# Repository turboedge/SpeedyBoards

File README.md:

# SpeedyBoards
WTMtronics has developed several EMS PCBs designed to use the Speeduino firmware.
The Speeduino code is available here [Speeduino](https://github.com/noisymime/speeduino), but the easiest way to load the code onto your ECU is to use [SpeedyLoader](https://github.com/speeduino/SpeedyLoader).
## Ocelot
The latest ECU designed by WTMtronics builds on the UA4C that came before it, and in fact if you compare the two side by side you will see many similarities. However there have been many improvements over the previous model which are outlined in the list below.
- Automotive connector
- Reduced size
- Integrated microcontroller
- VSS input
- Flyback diodes
- Reset button

The reset button was added as the only reset connection made to the microcontroller to prevent unwanted resets from USB connected devices. There is a caveat to this arrangement though. While the first time a firmware is loaded it will go on without intervention, subsequent times will require the user to hold the reset button down then release the button when the program starts the upload process. If the upload does not start right away go back and try again.

The Ocelot uses the Silicon Labs CP2102N USB to UART controller chip. Most modern computers will detect and automatically load a driver for the COM port. If you are not getting the COM port, then you can download drivers from their website [Silicon Labs Drivers](https://www.silabs.com/developers/usb-to-uart-bridge-vcp-drivers).

Latest version: A3 *First release
### Errata
vA3:
- Labeling for trigger jumpers is reversed. The secondary trigger jumpers are nearest the outside edge of the board, and the primary trigger jumpers are near the trigger conditioner socket.
- Serial numbers prior to 002287 will not operate with out a USB connection if no Bluetooth adapter is attached. If your serial number is 002287 or higher this issue does not affect your unit. If you are affected by this issue, please contact us so we can help you [WTMtronics Help](https://wtmtronics.com/help).
## UA4C
The Under Arduino Four Channel was designed to be as small as possible wile still using a standard off the shelf Arduino MEGA and Hammond extruded enclosure. This was achieved by using SMD components and placing the Arduino upside-down on top of the PCB. The unique stacking arrangement allows the unit to be particularly thin for a unit that still uses a separate Arduino MEGA. It is a 4+4 board that incorporates the follow features.
- Four injector channels
- Four ignitor channels
- Outputs for VVT, 2x PWM idle, boost, fuel pump, tachometer, and 2x fan
- Four auxiliary outputs
- Built in stepper idle control (versions C)
- Two trigger inputs
- Launch input
- Two additional interrupt input designated as flex and knock*
- Analog inputs for CLT, IAT, TPS, and O2
- Two auxiliary analog inputs
- MAP and baro sensor onboard
- Two GPIO connections that breakout inside the case

Latest version: C6

*Knock is currently unsupported in the firmware. Either input can be used for VSS.
## NO2C
The No Overhang Two Channel was designed to incorporate as many features as possible into a through-hole board that does not exceed the dimensions of the Arduino MEGA microcontroller it sits on top of. It is a 2+2 channel board that incorporates the features below.
- Two injector channels
- Two ignitor channels
- Outputs for VVT PWM idle, boost, fuel pump, and tachometer
- Two trigger inputs
- Launch input
- Analog inputs for CLT, IAT, TPS, and O2
- MAP sensor onboard
- Socket for stepper idle control module

Latest version: D1

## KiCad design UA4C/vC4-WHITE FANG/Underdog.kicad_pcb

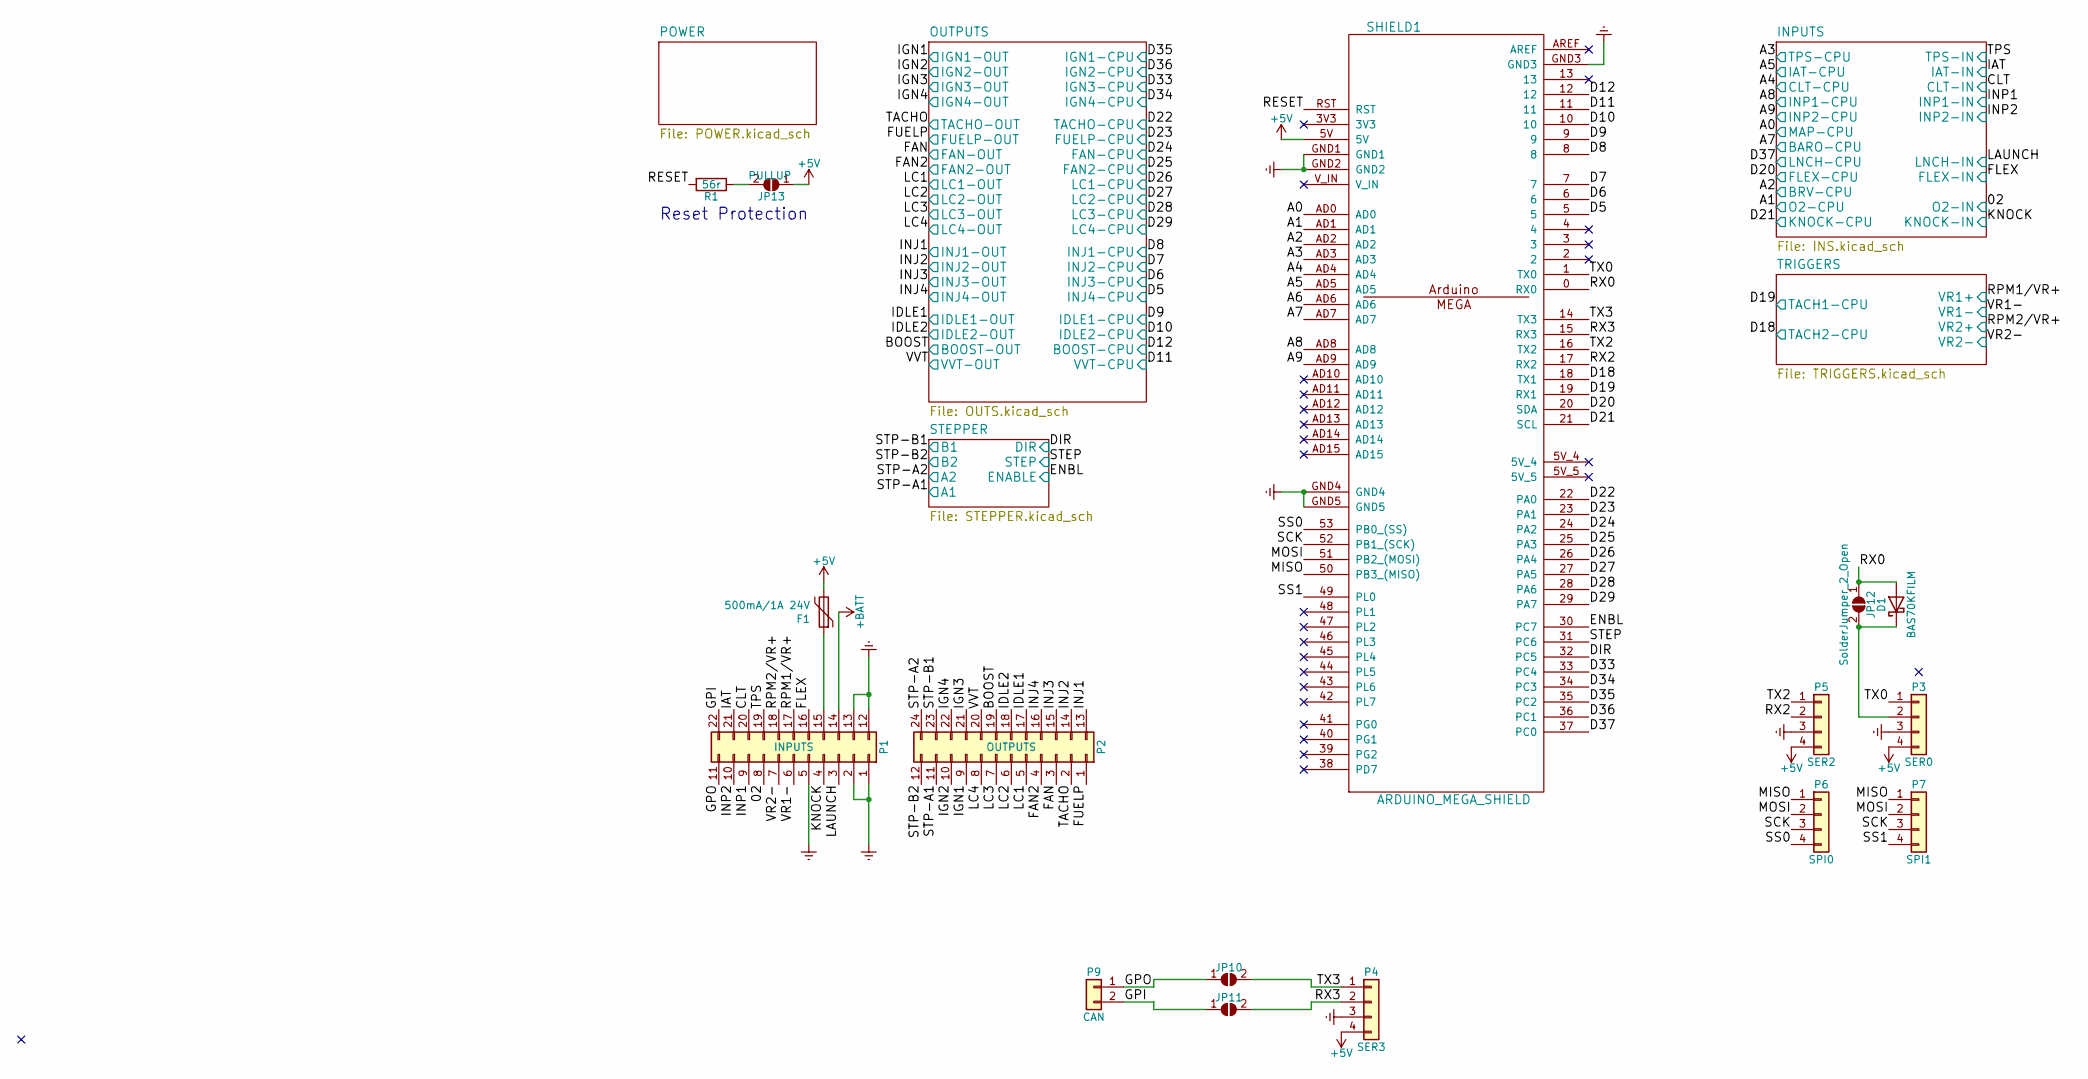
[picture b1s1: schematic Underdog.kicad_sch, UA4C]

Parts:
D1: BAS70KFILM; D_SOD-523; MPN BAS70-02V-V-G-08
F1: 500mA/1A 24V; Fuse_1206_3216Metric; MPN 0ZCJ0050AF2E
JP10, JP11, JP12: SolderJumper_2_Open; SolderJumper-2_P1.3mm_Open_Pad1.0x1.5mm; MPN DNP
JP13: PULLUP; JPR_2POS_SMLHL; MPN DNP
P1: INPUTS; Molex_Micro-Fit_3.0_43045-2200_2x11_P3.00mm_Horizontal; MPN DNP
P2: OUTPUTS; Molex_Micro-Fit_3.0_43045-2400_2x12_P3.00mm_Horizontal; MPN DNP
P3: SER0; Pin_Header_Straight_1x04_Pitch2.54mm; MPN DNP
P4: SER3; Pin_Header_Straight_1x04_Pitch2.54mm; MPN DNP
P5: SER2; Pin_Header_Straight_1x04_Pitch2.54mm; MPN DNP
P6: SPI0; Pin_Header_Straight_1x04_Pitch2.54mm; MPN DNP
P7: SPI1; Pin_Header_Straight_1x04_Pitch2.54mm; MPN DNP
P9: CAN; PinHeader_1x02_P2.54mm_Vertical; MPN DNP
R1: 56r; R_1206_3216Metric; MPN RK73H2BTTD56R0F
SHIELD1: ARDUINO_MEGA_SHIELD; MPN DNP

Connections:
+5V: F1.2, JP13.1 (A), P3.4, P4.4, P5.4, SHIELD1.5V; also elsewhere on the board
+BATT: P1.14; also elsewhere on the board
/02: P1.8; also elsewhere on the board
/A0: SHIELD1.AD0; also elsewhere on the board
/A1: SHIELD1.AD1; also elsewhere on the board
/A2: SHIELD1.AD2; also elsewhere on the board
/A3: SHIELD1.AD3; also elsewhere on the board
/A4: SHIELD1.AD4; also elsewhere on the board
/A5: SHIELD1.AD5; also elsewhere on the board
/A6: SHIELD1.AD6
/A7: SHIELD1.AD7; also elsewhere on the board
/A8: SHIELD1.AD8; also elsewhere on the board
/A9: SHIELD1.AD9; also elsewhere on the board
/BOOST: P2.19; also elsewhere on the board
/CLT: P1.20; also elsewhere on the board
/D5: SHIELD1.5; also elsewhere on the board
/D6: SHIELD1.6; also elsewhere on the board
/D7: SHIELD1.7; also elsewhere on the board
/D8: SHIELD1.8; also elsewhere on the board
/D9: SHIELD1.9; also elsewhere on the board
/D10: SHIELD1.10; also elsewhere on the board
/D11: SHIELD1.11; also elsewhere on the board
/D12: SHIELD1.12; also elsewhere on the board
/D18: SHIELD1.18 (TX1); also elsewhere on the board
/D19: SHIELD1.19 (RX1); also elsewhere on the board
/D20: SHIELD1.20 (SDA); also elsewhere on the board
/D21: SHIELD1.21 (SCL); also elsewhere on the board
/D22: SHIELD1.22 (PA0); also elsewhere on the board
/D23: SHIELD1.23 (PA1); also elsewhere on the board
/D24: SHIELD1.24 (PA2); also elsewhere on the board
/D25: SHIELD1.25 (PA3); also elsewhere on the board
/D26: SHIELD1.26 (PA4); also elsewhere on the board
/D27: SHIELD1.27 (PA5); also elsewhere on the board
/D28: SHIELD1.28 (PA6); also elsewhere on the board
/D29: SHIELD1.29 (PA7); also elsewhere on the board
/D33: SHIELD1.33 (PC4); also elsewhere on the board
/D34: SHIELD1.34 (PC3); also elsewhere on the board
/D35: SHIELD1.35 (PC2); also elsewhere on the board
/D36: SHIELD1.36 (PC1); also elsewhere on the board
/D37: SHIELD1.37 (PC0); also elsewhere on the board
/DIR: SHIELD1.32 (PC5); also elsewhere on the board
/ENBL: SHIELD1.30 (PC7); also elsewhere on the board
/FAN: P2.3; also elsewhere on the board
/FAN2: P2.4; also elsewhere on the board
/FLEX: P1.16; also elsewhere on the board
/FUELP: P2.1; also elsewhere on the board
/GPI: JP11.1 (A), P1.22, P9.2
/GPO: JP10.1 (A), P1.11, P9.1
/IAT: P1.21; also elsewhere on the board
/IDLE1: P2.17; also elsewhere on the board
/IDLE2: P2.18; also elsewhere on the board
/IGN1: P2.9; also elsewhere on the board
/IGN2: P2.10; also elsewhere on the board
/IGN3: P2.21; also elsewhere on the board
/IGN4: P2.22; also elsewhere on the board
/INJ1: P2.13; also elsewhere on the board
/INJ2: P2.14; also elsewhere on the board
/INJ3: P2.15; also elsewhere on the board
/INJ4: P2.16; also elsewhere on the board
/INP1: P1.9; also elsewhere on the board
/INP2: P1.10; also elsewhere on the board
/KNOCK: P1.4; also elsewhere on the board
/LAUNCH: P1.3; also elsewhere on the board
/LC1: P2.5; also elsewhere on the board
/LC2: P2.6; also elsewhere on the board
/LC3: P2.7; also elsewhere on the board
/LC4: P2.8; also elsewhere on the board
/MISO: P6.1, P7.1, SHIELD1.50 (PB3_(MISO))
/MOSI: P6.2, P7.2, SHIELD1.51 (PB2_(MOSI))
/RESET: R1.2, SHIELD1.RST
/RPM1/VR+: P1.17; also elsewhere on the board
/RPM2/VR+: P1.18; also elsewhere on the board
/RX0: D1.2 (A), JP12.1 (A), SHIELD1.0 (RX0)
/RX2: P5.2, SHIELD1.17 (RX2)
/RX3: JP11.2 (B), P4.2, SHIELD1.15 (RX3)
/SCK: P6.3, P7.3, SHIELD1.52 (PB1_(SCK))
/SS0: P6.4, SHIELD1.53 (PB0_(SS))
/SS1: P7.4, SHIELD1.49 (PL0)
/STEP: SHIELD1.31 (PC6); also elsewhere on the board
/STP-A1: P2.11; also elsewhere on the board
/STP-A2: P2.24; also elsewhere on the board
/STP-B1: P2.23; also elsewhere on the board
/STP-B2: P2.12; also elsewhere on the board
/TACHO: P2.2; also elsewhere on the board
/TPS: P1.19; also elsewhere on the board
/TX0: P3.1, SHIELD1.1 (TX0)
/TX2: P5.1, SHIELD1.16 (TX2)
/TX3: JP10.2 (B), P4.1, SHIELD1.14 (TX3)
/VR1-: P1.6; also elsewhere on the board
/VR2-: P1.7; also elsewhere on the board
/VVT: P2.20; also elsewhere on the board
Earth: P1.1, P1.2, P1.5, P1.12, P1.13, P3.3, P4.3, P5.3, SHIELD1.GND1, SHIELD1.GND2, SHIELD1.GND3, SHIELD1.GND4, SHIELD1.GND5; also elsewhere on the board
unnamed: D1.1 (K), JP12.2 (B), P3.2
unnamed: F1.1, P1.15
unnamed: JP13.2 (B), R1.1

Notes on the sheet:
Reset Protection

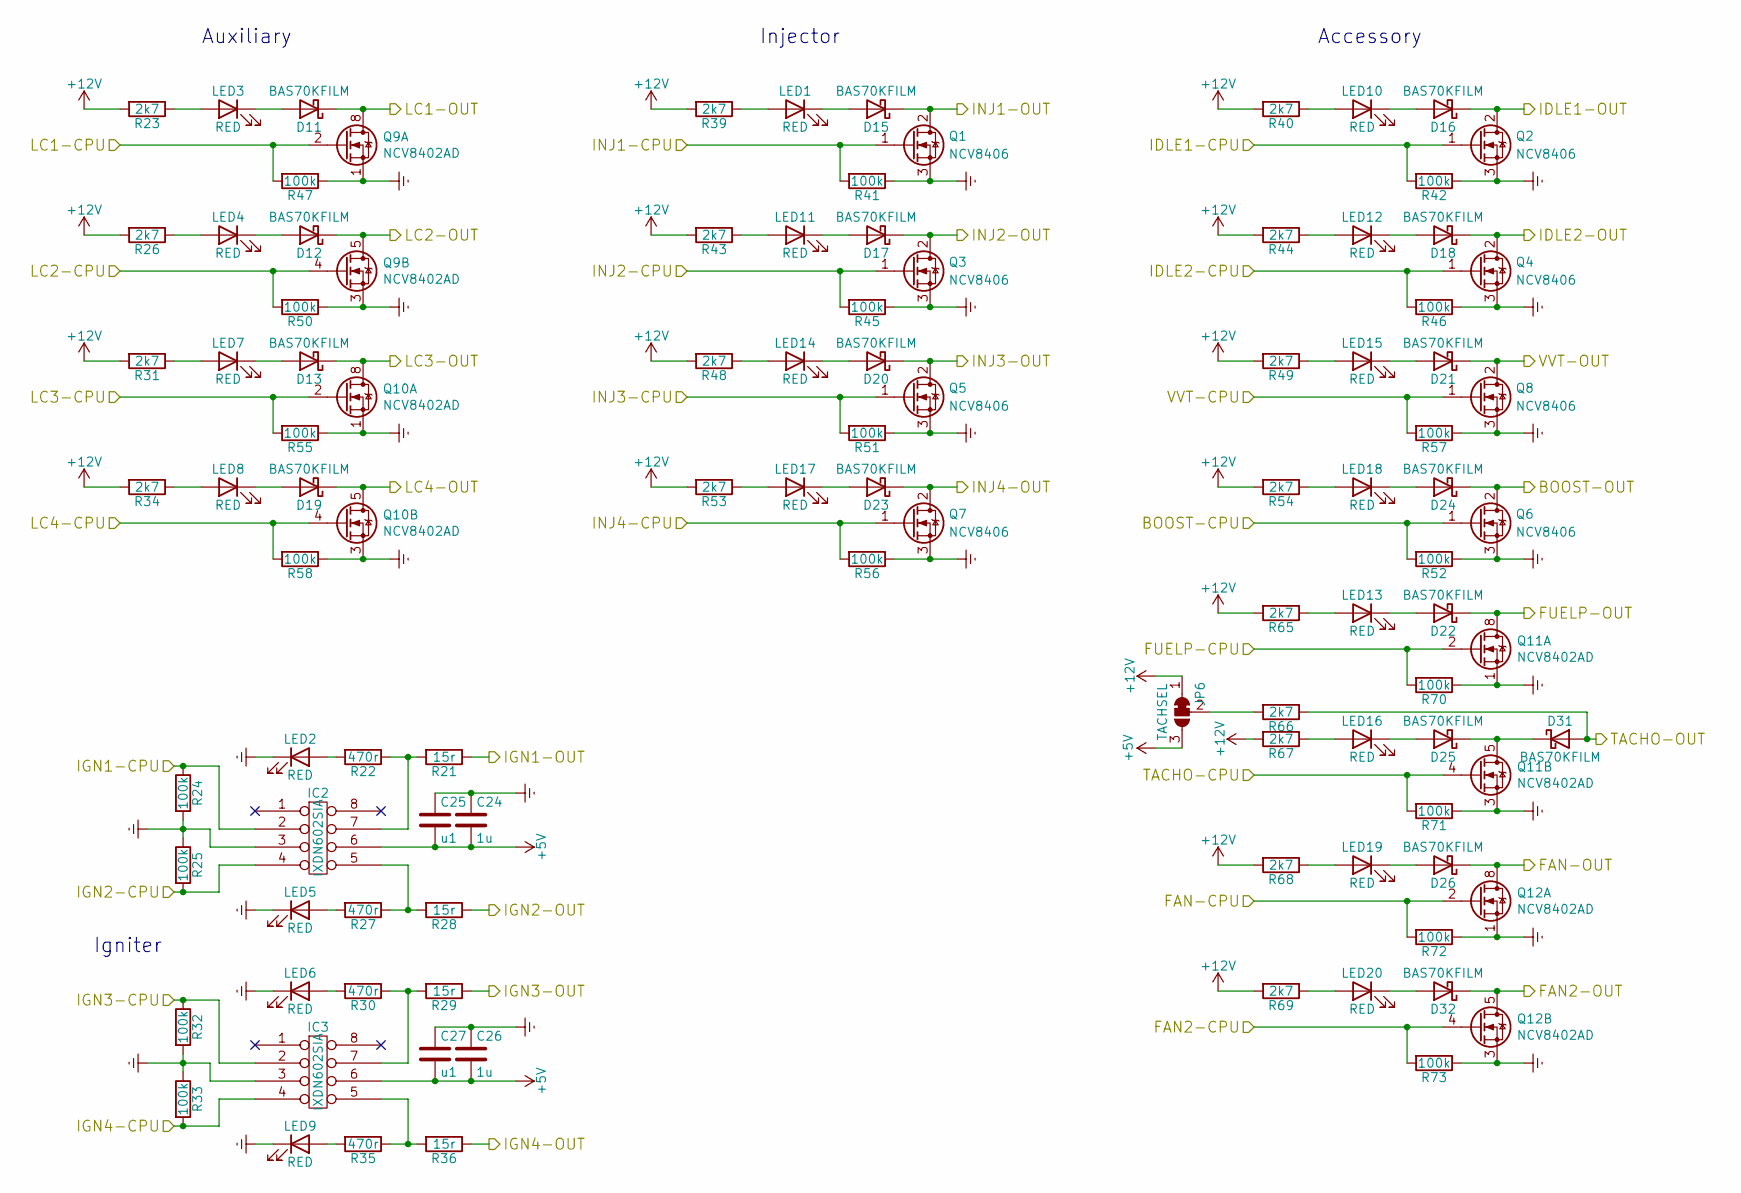
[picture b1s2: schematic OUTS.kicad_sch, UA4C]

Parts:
C24, C26: 1u; C_0805_2012Metric; MPN CL21B105KBFNNNE
C25, C27: u1; C_0805_2012Metric; MPN CL21B104KBFNNNE
D11, D12, D13, D15, D16, D17, D18, D19, D20, D21, D22, D23, D24, D25, D26, D31, D32: BAS70KFILM; D_SOD-523; MPN BAS70-02V-V-G-08
IC2, IC3: IXDN602SIA; SOIC-8_3.9x4.9mm_P1.27mm; MPN IXDN602SIA
JP6: TACHSEL; SolderJumper-3_P1.3mm_Bridged12_Pad1.0x1.5mm_NumberLabels; MPN DNP
LED1, LED2, LED3, LED4, LED5, LED6, LED7, LED8, LED9, LED10, LED11, LED12, LED13, LED14, LED15, LED16, LED17, LED18, LED19, LED20: RED; LED_0603_1608Metric; MPN SML-310LTT86
Q1, Q2, Q3, Q4, Q5, Q6, Q7, Q8: NCV8406; TO-252-3_TabPin2; MPN NCV8406BDTRKG
Q9, Q10, Q11, Q12: NCV8402AD; SOIC-8_3.9x4.9mm_P1.27mm; MPN NCV8402ADDR2G
R21, R28, R29, R36: 15r; R_2512_6332Metric; MPN RK73H3ATTE15R0F
R22, R27, R30, R35: 470r; R_0805_2012Metric; MPN RK73H2ATTD4700F
R23, R26, R31, R34, R39, R40, R43, R44, R48, R49, R53, R54, R65, R66, R67, R68, R69: 2k7; R_0603_1608Metric; MPN RK73B1JTTD272J
R24, R25, R32, R33, R41, R42, R45, R46, R47, R50, R51, R52, R55, R56, R57, R58, R70, R71, R72, R73: 100k; R_0603_1608Metric; MPN RK73B1JTTD104J

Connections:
+5V: C24.2, C25.2, C26.2, C27.2, IC2.6, IC3.6, JP6.3 (B); also elsewhere on the board
+12V: JP6.1 (A), R23.2, R26.2, R31.2, R34.2, R39.2, R40.2, R43.2, R44.2, R48.2, R49.2, R53.2, R54.2, R65.2, R67.2, R68.2, R69.2; also elsewhere on the board
/BOOST: D24.1 (K), Q6.2 (D); also elsewhere on the board
/D5: Q7.1 (G), R56.2; also elsewhere on the board
/D6: Q5.1 (G), R51.2; also elsewhere on the board
/D7: Q3.1 (G), R45.2; also elsewhere on the board
/D8: Q1.1 (G), R41.2; also elsewhere on the board
/D9: Q2.1 (G), R42.2; also elsewhere on the board
/D10: Q4.1 (G), R46.2; also elsewhere on the board
/D11: Q8.1 (G), R57.2; also elsewhere on the board
/D12: Q6.1 (G), R52.2; also elsewhere on the board
/D22: Q11.4 (G2), R71.2; also elsewhere on the board
/D23: Q11.2 (G1), R70.2; also elsewhere on the board
/D24: Q12.2 (G1), R72.2; also elsewhere on the board
/D25: Q12.4 (G2), R73.2; also elsewhere on the board
/D26: Q9.2 (G1), R47.2; also elsewhere on the board
/D27: Q9.4 (G2), R50.2; also elsewhere on the board
/D28: Q10.2 (G1), R55.2; also elsewhere on the board
/D29: Q10.4 (G2), R58.2; also elsewhere on the board
/D33: IC3.2, R32.1; also elsewhere on the board
/D34: IC3.4, R33.2; also elsewhere on the board
/D35: IC2.2, R24.1; also elsewhere on the board
/D36: IC2.4, R25.2; also elsewhere on the board
/FAN: D26.1 (K), Q12.7 (D1), Q12.8 (D1); also elsewhere on the board
/FAN2: D32.1 (K), Q12.5 (D2), Q12.6 (D2); also elsewhere on the board
/FUELP: D22.1 (K), Q11.7 (D1), Q11.8 (D1); also elsewhere on the board
/IDLE1: D16.1 (K), Q2.2 (D); also elsewhere on the board
/IDLE2: D18.1 (K), Q4.2 (D); also elsewhere on the board
/IGN1: R21.1; also elsewhere on the board
/IGN2: R28.1; also elsewhere on the board
/IGN3: R29.1; also elsewhere on the board
/IGN4: R36.1; also elsewhere on the board
/INJ1: D15.1 (K), Q1.2 (D); also elsewhere on the board
/INJ2: D17.1 (K), Q3.2 (D); also elsewhere on the board
/INJ3: D20.1 (K), Q5.2 (D); also elsewhere on the board
/INJ4: D23.1 (K), Q7.2 (D); also elsewhere on the board
/LC1: D11.1 (K), Q9.7 (D1), Q9.8 (D1); also elsewhere on the board
/LC2: D12.1 (K), Q9.5 (D2), Q9.6 (D2); also elsewhere on the board
/LC3: D13.1 (K), Q10.7 (D1), Q10.8 (D1); also elsewhere on the board
/LC4: D19.1 (K), Q10.5 (D2), Q10.6 (D2); also elsewhere on the board
/TACHO: D31.2 (A), R66.1; also elsewhere on the board
/VVT: D21.1 (K), Q8.2 (D); also elsewhere on the board
Earth: C24.1, C25.1, C26.1, C27.1, IC2.3, IC3.3, LED2.1 (K), LED5.1 (K), LED6.1 (K), LED9.1 (K), Q1.3 (S), Q2.3 (S), Q3.3 (S), Q4.3 (S), Q5.3 (S), Q6.3 (S), Q7.3 (S), Q8.3 (S), Q9.1 (S1), Q9.3 (S2), Q10.1 (S1), Q10.3 (S2), Q11.1 (S1), Q11.3 (S2), Q12.1 (S1), Q12.3 (S2), R24.2, R25.1, R32.2, R33.1, R41.1, R42.1, R45.1, R46.1, R47.1, R50.1, R51.1, R52.1, R55.1, R56.1, R57.1, R58.1, R70.1, R71.1, R72.1, R73.1; also elsewhere on the board
unnamed: D11.2 (A), LED3.1 (K)
unnamed: D12.2 (A), LED4.1 (K)
unnamed: D13.2 (A), LED7.1 (K)
unnamed: D15.2 (A), LED1.1 (K)
unnamed: D16.2 (A), LED10.1 (K)
unnamed: D17.2 (A), LED11.1 (K)
unnamed: D18.2 (A), LED12.1 (K)
unnamed: D19.2 (A), LED8.1 (K)
unnamed: D20.2 (A), LED14.1 (K)
unnamed: D21.2 (A), LED15.1 (K)
unnamed: D22.2 (A), LED13.1 (K)
unnamed: D23.2 (A), LED17.1 (K)
unnamed: D24.2 (A), LED18.1 (K)
unnamed: D25.1 (K), D31.1 (K), Q11.5 (D2), Q11.6 (D2)
unnamed: D25.2 (A), LED16.1 (K)
unnamed: D26.2 (A), LED19.1 (K)
unnamed: D32.2 (A), LED20.1 (K)
unnamed: IC2.5, R27.1, R28.2
unnamed: IC2.7, R21.2, R22.1
unnamed: IC3.5, R35.1, R36.2
unnamed: IC3.7, R29.2, R30.1
unnamed: JP6.2 (C), R66.2
unnamed: LED1.2 (A), R39.1
unnamed: LED2.2 (A), R22.2
unnamed: LED3.2 (A), R23.1
unnamed: LED4.2 (A), R26.1
unnamed: LED5.2 (A), R27.2
unnamed: LED6.2 (A), R30.2
unnamed: LED7.2 (A), R31.1
unnamed: LED8.2 (A), R34.1
unnamed: LED9.2 (A), R35.2
unnamed: LED10.2 (A), R40.1
unnamed: LED11.2 (A), R43.1
unnamed: LED12.2 (A), R44.1
unnamed: LED13.2 (A), R65.1
unnamed: LED14.2 (A), R48.1
unnamed: LED15.2 (A), R49.1
unnamed: LED16.2 (A), R67.1
unnamed: LED17.2 (A), R53.1
unnamed: LED18.2 (A), R54.1
unnamed: LED19.2 (A), R68.1
unnamed: LED20.2 (A), R69.1

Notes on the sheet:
Accessory
Auxiliary
Injector
Igniter

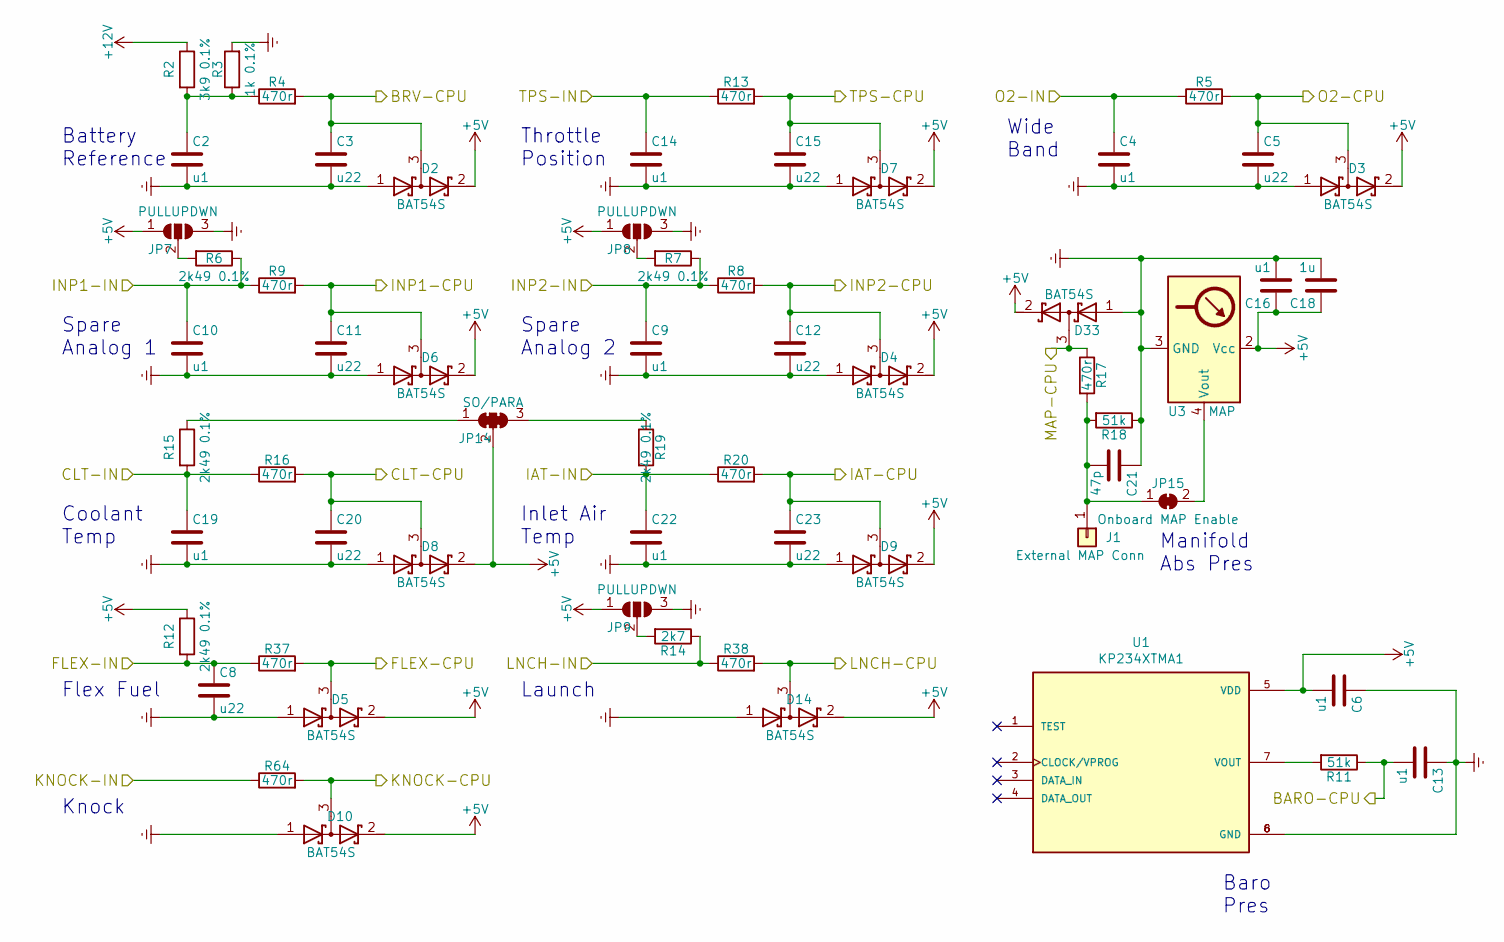
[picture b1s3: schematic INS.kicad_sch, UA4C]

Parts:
C2, C4, C6, C9, C10, C13, C14, C16, C19, C22: u1; C_0805_2012Metric; MPN CL21B104KBFNNNE
C3, C5, C8, C11, C12, C15, C20, C23: u22; C_0805_2012Metric; MPN CL21B224KBFNNNE
C18: 1u; C_0805_2012Metric; MPN CL21B105KBFNNNE
C21: 47p; C_0805_2012Metric; MPN CL21C470JBANNNC
D2, D3, D4, D5, D6, D7, D8, D9, D10, D14, D33: BAT54S; SOT-23; MPN BAT54S,215
J1: External MAP Conn; SolderWirePad_single_1mmDrill; MPN DNP
JP7, JP8, JP9: PULLUPDWN; SolderJumper-3_P1.3mm_Open_Pad1.0x1.5mm_NumberLabels; MPN DNP
JP14: SO/PARA; SolderJumper-3_P1.3mm_Bridged123_Pad1.0x1.5mm_NumberLabels; MPN DNP
JP15: Onboard MAP Enable; SolderJumper-2_P1.3mm_Bridged_Pad1.0x1.5mm; MPN DNP
R2: 3k9 0.1%; R_0805_2012Metric; MPN ERA6AEB392V
R3: 1k 0.1%; R_0805_2012Metric; MPN ERA6AEB102V
R4, R5, R8, R9, R13, R16, R17, R20, R37, R38, R64: 470r; R_0805_2012Metric; MPN RK73H2ATTD4700F
R6, R7, R12, R15, R19: 2k49 0.1%; R_0805_2012Metric; MPN ERA6AEB2491V
R11, R18: 51k; R_0805_2012Metric; MPN RK73H2ATTD5102F
R14: 2k7; R_0603_1608Metric; MPN RK73B1JTTD272J
U1: KP234XTMA1; XDCR_KP234XTMA1; PARTREV 1.0
U3: MAP; NXP_Pressure_Sensor_SSOP; MPN MPXH6400AC6U

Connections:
+5V: C6.2, C16.1, C18.1, D2.2 (K), D3.2 (K), D4.2 (K), D5.2 (K), D6.2 (K), D7.2 (K), D8.2 (K), D9.2 (K), D10.2 (K), D14.2 (K), D33.2 (K), JP7.1 (A), JP8.1 (A), JP9.1 (A), JP14.2 (C), R12.1, U1.5 (VDD), U3.2 (Vcc); also elsewhere on the board
+12V: R2.1; also elsewhere on the board
/02: C4.1, R5.1; also elsewhere on the board
/A0: D33.3 (common), R17.1; also elsewhere on the board
/A1: C5.1, D3.3 (common), R5.2; also elsewhere on the board
/A2: C3.1, D2.3 (common), R4.2; also elsewhere on the board
/A3: C15.1, D7.3 (common), R13.2; also elsewhere on the board
/A4: C20.1, D8.3 (common), R16.2; also elsewhere on the board
/A5: C23.1, D9.3 (common), R20.2; also elsewhere on the board
/A7: C13.2, R11.1; also elsewhere on the board
/A8: C11.1, D6.3 (common), R9.2; also elsewhere on the board
/A9: C12.1, D4.3 (common), R8.2; also elsewhere on the board
/CLT: C19.1, R15.2, R16.1; also elsewhere on the board
/D20: D5.3 (common), R37.2; also elsewhere on the board
/D21: D10.3 (common), R64.2; also elsewhere on the board
/D37: D14.3 (common), R38.2; also elsewhere on the board
/FLEX: C8.1, R12.2, R37.1; also elsewhere on the board
/IAT: C22.1, R19.2, R20.1; also elsewhere on the board
/INP1: C10.1, R6.1, R9.1; also elsewhere on the board
/INP2: C9.1, R7.1, R8.1; also elsewhere on the board
/KNOCK: R64.1; also elsewhere on the board
/LAUNCH: R14.1, R38.1; also elsewhere on the board
/TPS: C14.1, R13.1; also elsewhere on the board
Earth: C2.2, C3.2, C4.2, C5.2, C6.1, C8.2, C9.2, C10.2, C11.2, C12.2, C13.1, C14.2, C15.2, C16.2, C18.2, C19.2, C20.2, C21.1, C22.2, C23.2, D2.1 (A), D3.1 (A), D4.1 (A), D5.1 (A), D6.1 (A), D7.1 (A), D8.1 (A), D9.1 (A), D10.1 (A), D14.1 (A), D33.1 (A), JP7.3 (B), JP8.3 (B), JP9.3 (B), R3.2, R18.1, U1.6 (GND), U1.8 (GND), U3.3 (GND); also elsewhere on the board
unnamed: C2.1, R2.2, R3.1, R4.1
unnamed: C21.2, J1.1, JP15.1 (A), R17.2, R18.2
unnamed: JP7.2 (C), R6.2
unnamed: JP8.2 (C), R7.2
unnamed: JP9.2 (C), R14.2
unnamed: JP14.1 (A), R15.1
unnamed: JP14.3 (B), R19.1
unnamed: JP15.2 (B), U3.4 (Vout)
unnamed: R11.2, U1.7 (VOUT)

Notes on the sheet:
Throttle Position
Knock
Inlet Air Temp
Wide Band
Flex Fuel
Battery Reference
Coolant Temp
Launch
Manifold Abs Pres
Spare Analog 1
Spare Analog 2
Baro Pres

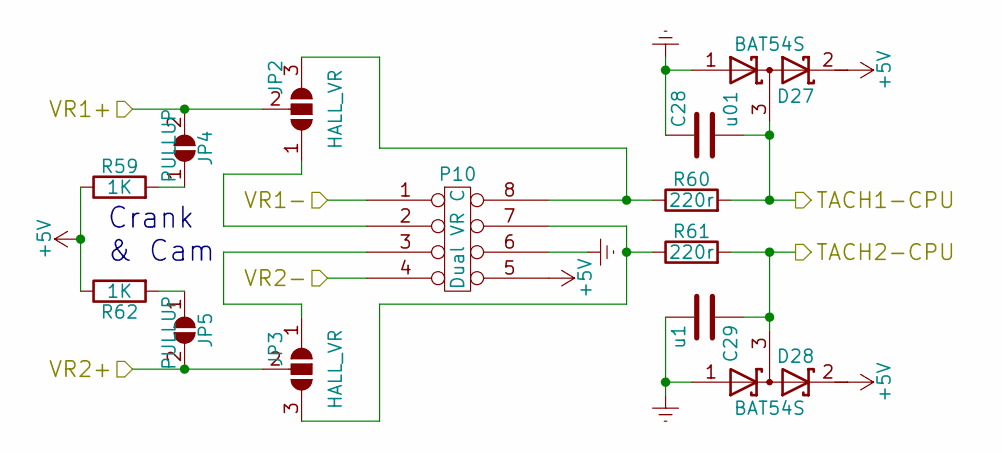
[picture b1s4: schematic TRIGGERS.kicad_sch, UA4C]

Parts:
C28: u01; C_0805_2012Metric; MPN CL21B103KBCNNNC
C29: u1; C_0805_2012Metric; MPN CL21B104KBFNNNE
D27, D28: BAT54S; SOT-23; MPN BAT54S,215
JP2, JP3: HALL_VR; JPR_3POS_SMLHL; MPN DNP
JP4, JP5: PULLUP; JPR_2POS_SMLHL; MPN DNP
P10: Dual VR C; DIP-8_W7.62mm_Socket; MPN DNP
R59, R62: 1K; R_0805_2012Metric; MPN RK73H2ATTD1001F
R60, R61: 220r; R_0805_2012Metric; MPN RK73H2ATTD2200F

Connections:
+5V: D27.2 (K), D28.2 (K), P10.5, R59.1, R62.1; also elsewhere on the board
/D18: C29.1, D28.3 (common), R61.2; also elsewhere on the board
/D19: C28.2, D27.3 (common), R60.2; also elsewhere on the board
/RPM1/VR+: JP2.2 (C), JP4.2 (B); also elsewhere on the board
/RPM2/VR+: JP3.2 (C), JP5.2 (B); also elsewhere on the board
/VR1-: P10.1; also elsewhere on the board
/VR2-: P10.4; also elsewhere on the board
Earth: C28.1, C29.2, D27.1 (A), D28.1 (A), P10.6; also elsewhere on the board
unnamed: JP2.1 (A), P10.2
unnamed: JP2.3 (B), P10.8, R60.1
unnamed: JP3.1 (A), P10.3
unnamed: JP3.3 (B), P10.7, R61.1
unnamed: JP4.1 (A), R59.2
unnamed: JP5.1 (A), R62.2

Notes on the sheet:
Crank & Cam

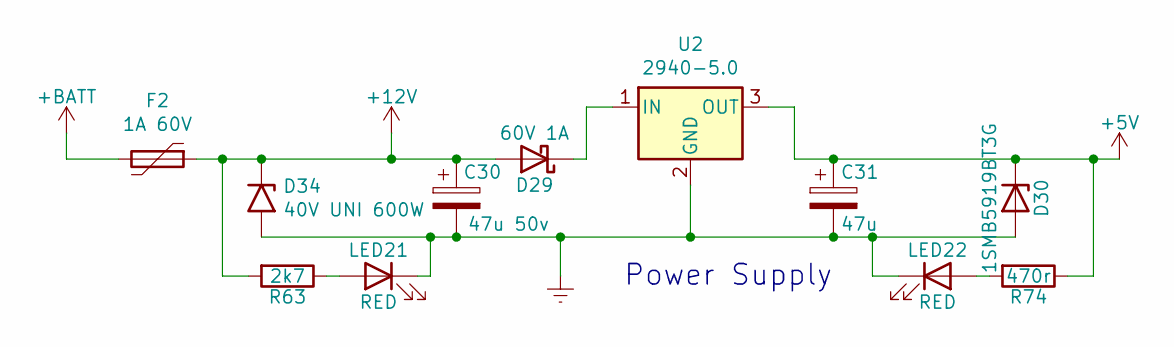
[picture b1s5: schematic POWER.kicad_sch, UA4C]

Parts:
C30: 47u 50v; CP_Elec_6.3x5.4; MPN EEE-FT1H470AL
C31: 47u; CP_EIA-3216-18_Kemet-A; MPN T55A476M6R3C0200
D29: 60V 1A; D_SMA; MPN B160-E3/61T
D30: 1SMB5919BT3G; D_SMB; MPN 1SMB5919BT3G
D34: 40V UNI 600W; D_SMB; MPN SMBJ40A
F2: 1A 60V; Fuse_2920_7451Metric_Castellated; MPN 0ZCF0100AF2A
LED21, LED22: RED; LED_0603_1608Metric; MPN SML-310LTT86
R63: 2k7; R_0603_1608Metric; MPN RK73B1JTTD272J
R74: 470r; R_0805_2012Metric; MPN RK73H2ATTD4700F
U2: 2940-5.0; TO-252-3_TabPin2

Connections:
+5V: C31.1, D30.1 (K), R74.1, U2.3 (OUT); also elsewhere on the board
+12V: C30.1, D29.2 (A), D34.1 (A1), F2.1, R63.2; also elsewhere on the board
+BATT: F2.2; also elsewhere on the board
Earth: C30.2, C31.2, D30.2 (A), D34.2 (A2), LED21.1 (K), LED22.1 (K), U2.2 (GND); also elsewhere on the board
unnamed: D29.1 (K), U2.1 (IN)
unnamed: LED21.2 (A), R63.1
unnamed: LED22.2 (A), R74.2

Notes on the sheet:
Power Supply

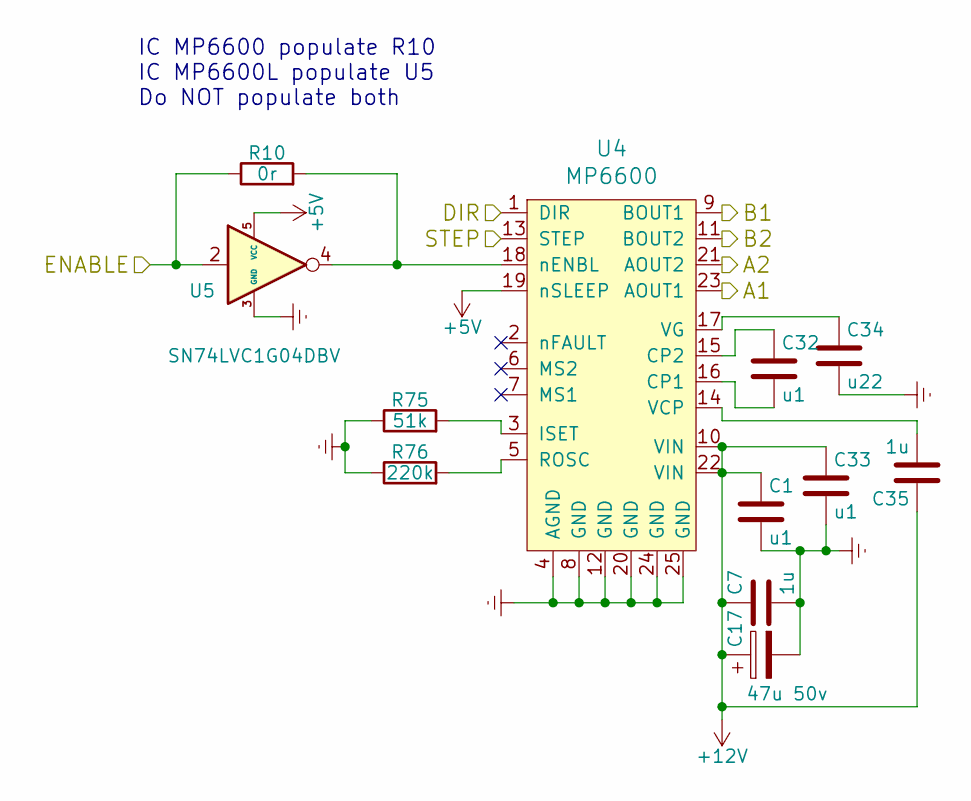
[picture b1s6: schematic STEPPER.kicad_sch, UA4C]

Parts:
C1, C32, C33: u1; C_0805_2012Metric; MPN CL21B104KBFNNNE
C7, C35: 1u; C_0805_2012Metric; MPN CL21B105KBFNNNE
C17: 47u 50v; CP_Elec_6.3x5.4; MPN EEE-FT1H470AL
C34: u22; C_0805_2012Metric; MPN CL21B224KBFNNNE
R10: 0r; R_0805_2012Metric
R75: 51k; R_0805_2012Metric; MPN RK73H2ATTD5102F
R76: 220k; R_0805_2012Metric; MPN RK73H2ATTD2203F
U4: MP6600; QFN-24-1EP_4x4mm_P0.5mm_EP2.7x2.7mm_ThermalVias; MPN MP6600GR-Z
U5: SN74LVC1G04DBV; SOT-23-5

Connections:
+5V: U4.19 (nSLEEP), U5.5 (VCC); also elsewhere on the board
+12V: C1.1, C7.1, C17.1, C33.1, C35.1, U4.10 (VIN), U4.22 (VIN); also elsewhere on the board
/DIR: U4.1 (DIR); also elsewhere on the board
/ENBL: R10.1, U5.2; also elsewhere on the board
/STEP: U4.13 (STEP); also elsewhere on the board
/STP-A1: U4.23 (AOUT1); also elsewhere on the board
/STP-A2: U4.21 (AOUT2); also elsewhere on the board
/STP-B1: U4.9 (BOUT1); also elsewhere on the board
/STP-B2: U4.11 (BOUT2); also elsewhere on the board
Earth: C1.2, C7.2, C17.2, C33.2, C34.2, R75.1, R76.1, U4.4 (AGND), U4.8 (GND), U4.12 (GND), U4.20 (GND), U4.24 (GND), U4.25 (GND), U5.3 (GND); also elsewhere on the board
unnamed: C32.1, U4.15 (CP2)
unnamed: C32.2, U4.16 (CP1)
unnamed: C34.1, U4.17 (VG)
unnamed: C35.2, U4.14 (VCP)
unnamed: R75.2, U4.3 (ISET)
unnamed: R76.2, U4.5 (ROSC)
unnamed: R10.2, U4.18 (nENBL), U5.4

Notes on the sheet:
IC MP6600 populate R10 IC MP6600L populate U5 Do NOT populate both

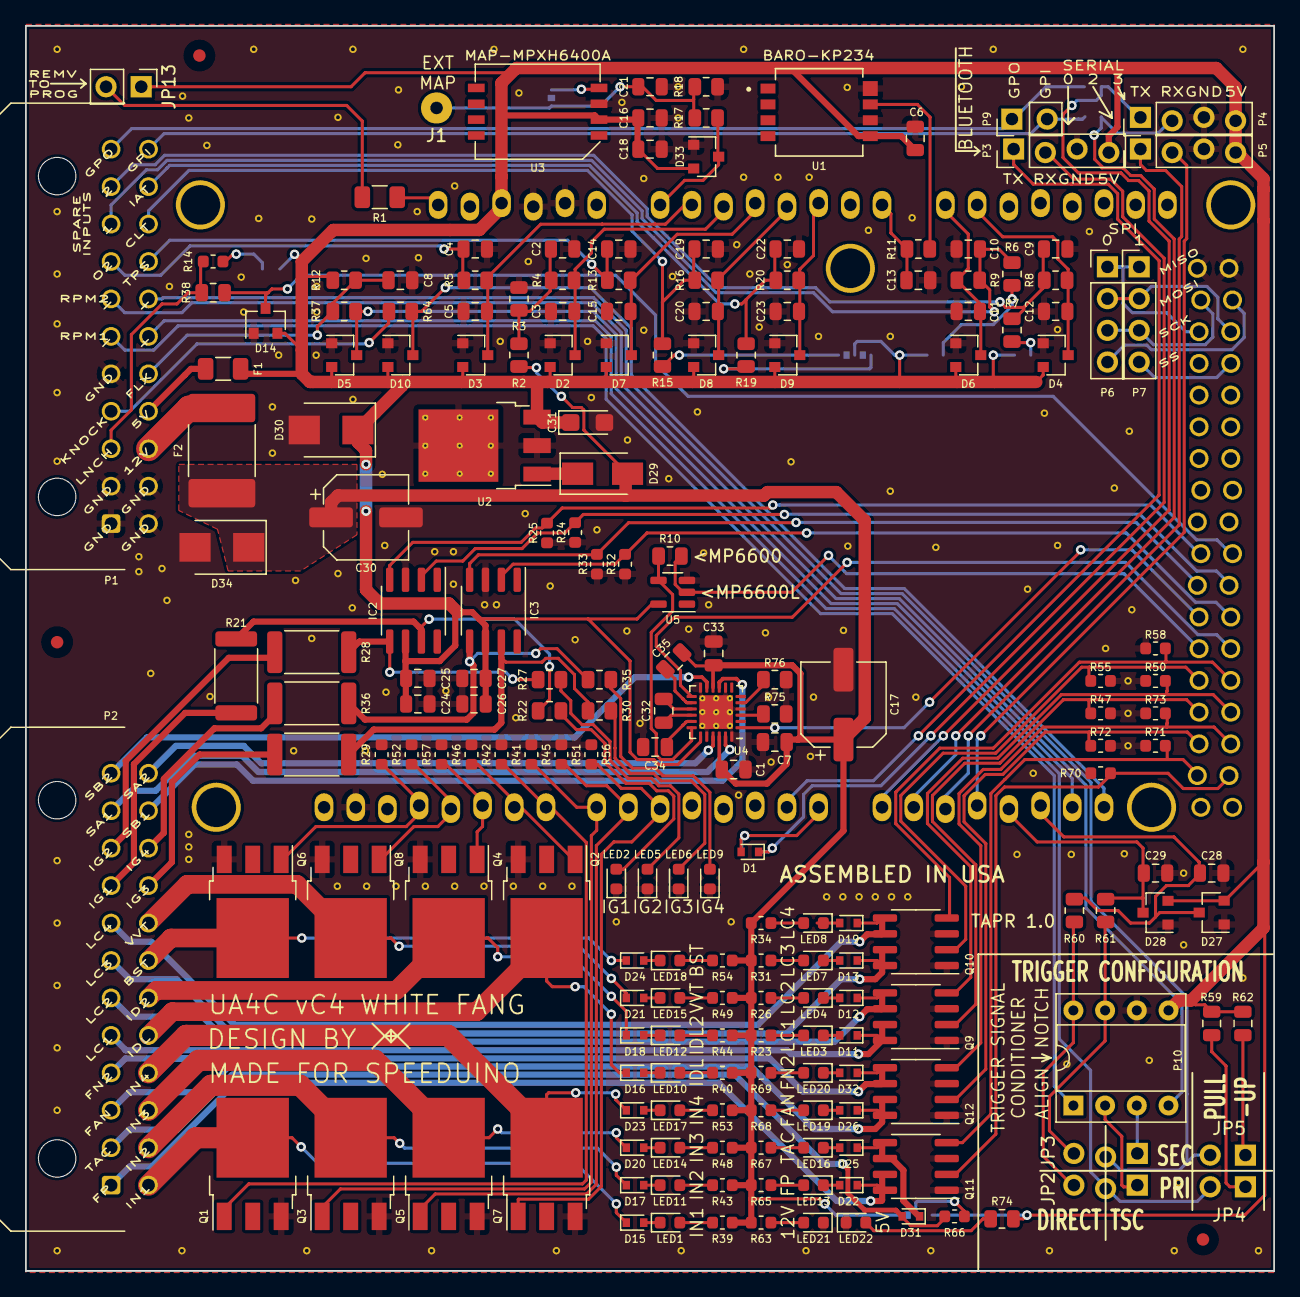
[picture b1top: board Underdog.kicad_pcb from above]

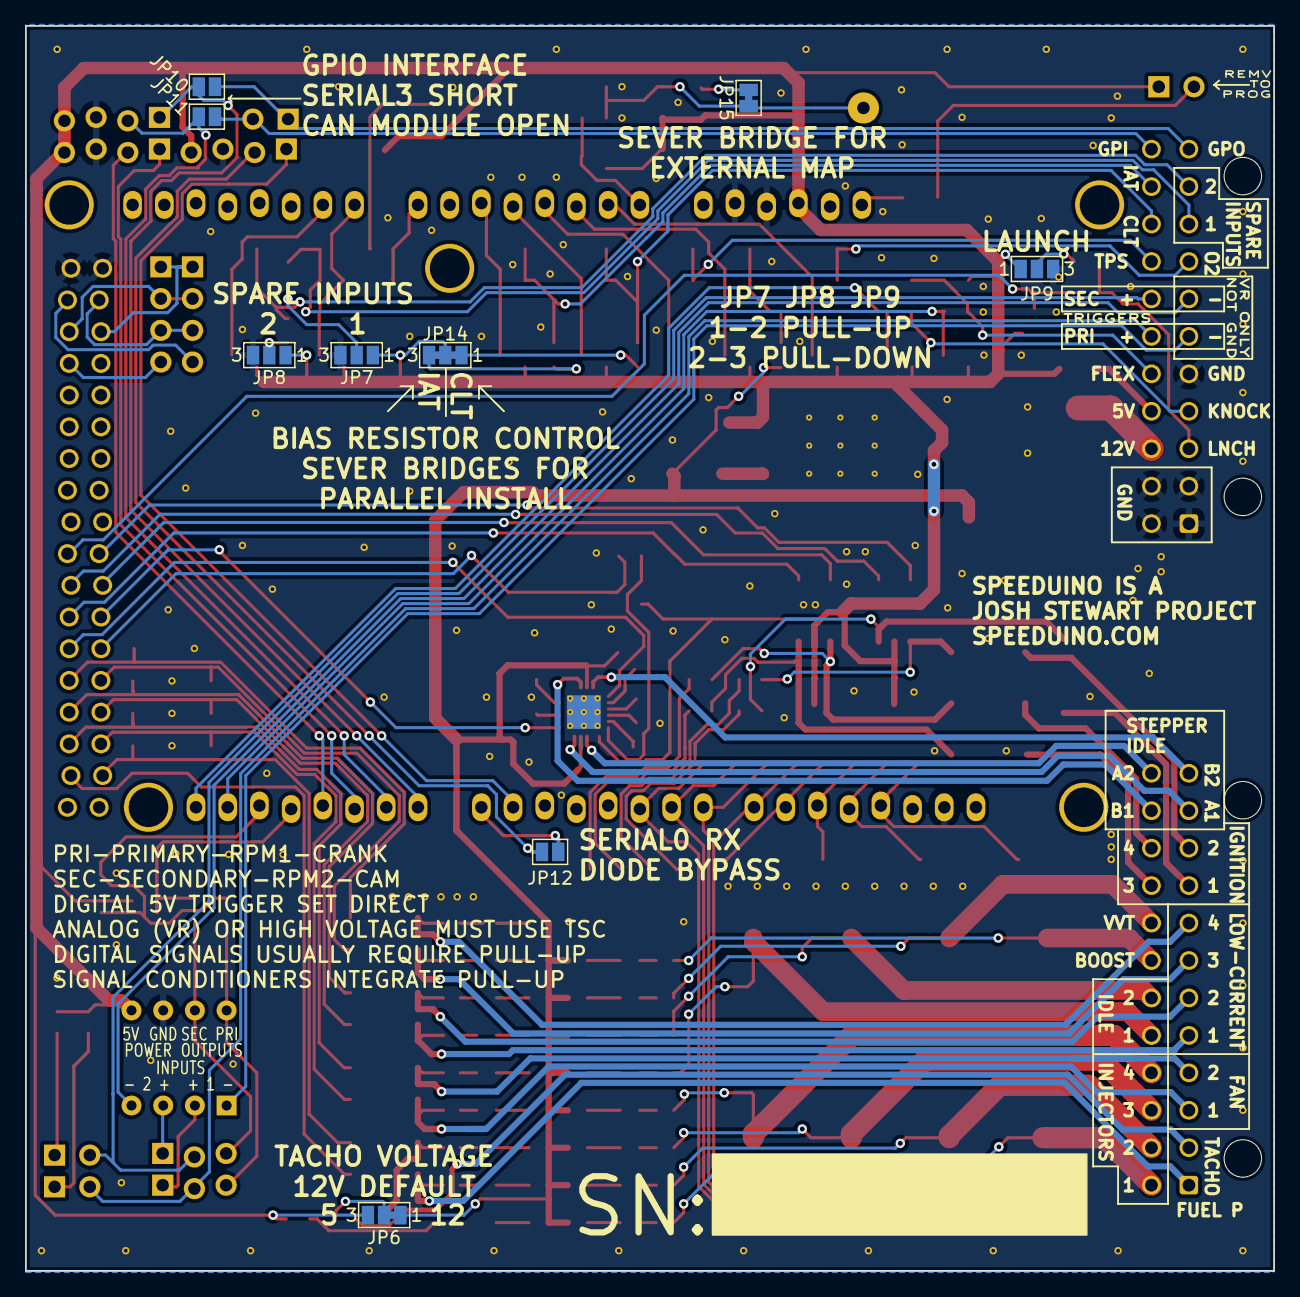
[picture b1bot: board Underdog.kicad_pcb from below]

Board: 2 copper layers, 100.0 x 99.8 mm, 213 parts (10 on the bottom side), 162 nets.
